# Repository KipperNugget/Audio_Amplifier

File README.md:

# ENGR 301 (Microelectronics Lab): Audio Amplifier

The goal of this project was to design, source components, and assemble an audio amplifier

EAGLE was utilized to design the pcb
LTspice was utilized for simulation

### Schematic

### Board
Please excuse the disgusting finish; attempted cleaning with isopropyl alcohol, but the flux continued to stain the board.

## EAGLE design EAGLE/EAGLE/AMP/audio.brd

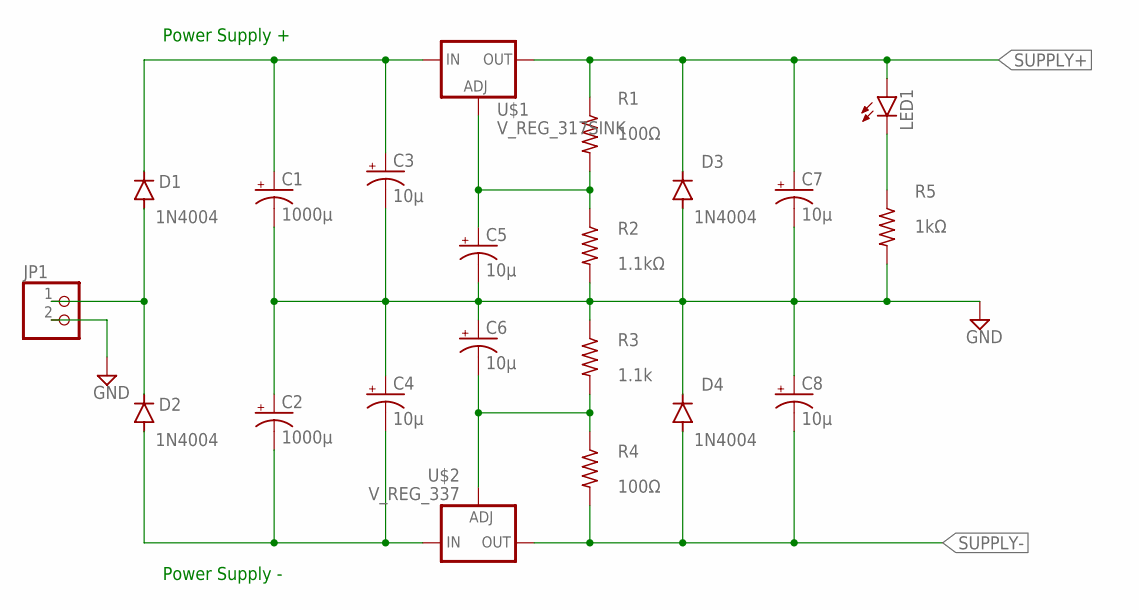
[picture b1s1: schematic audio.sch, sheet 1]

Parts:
C1, C2: 1000μ; E3,5-10
C3, C4, C5, C6, C7, C8: 10μ; E1,8-4
D1, D2, D3, D4: 1N4004; DO41-10
JP1: PINHD-1X2; 1X02
LED1: LED3MM
R1, R4: 100Ω; 0204/7
R2: 1.1kΩ; 0204/7
R3: 1.1k; 0204/7
R5: 1kΩ; 0204/7
U$1: V_REG_317SINK; TO220-ADJ
U$2: V_REG_337; TO220-ADJ-NEG

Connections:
GND: C1.-, C2.+, C3.-, C4.+, C5.-, C6.+, C7.-, C8.+, D3.A, D4.C, JP1.2, R2.2, R3.1, R5.2; also elsewhere on the board
unnamed: C1.+, C3.+, D1.C, U$1.IN
unnamed: C2.-, C4.-, D2.A, U$2.IN
unnamed: D1.A, D2.C, JP1.1
unnamed: C5.+, R1.2, R2.1, U$1.ADJ
unnamed: C6.-, R3.2, R4.1, U$2.ADJ
unnamed: LED1.K (C), R5.1
SUPPLY+: C7.+, D3.C, LED1.A, R1.1, U$1.OUT; also elsewhere on the board
SUPPLY-: C8.-, D4.A, R4.2, U$2.OUT; also elsewhere on the board

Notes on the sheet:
Power Supply -
Power Supply +

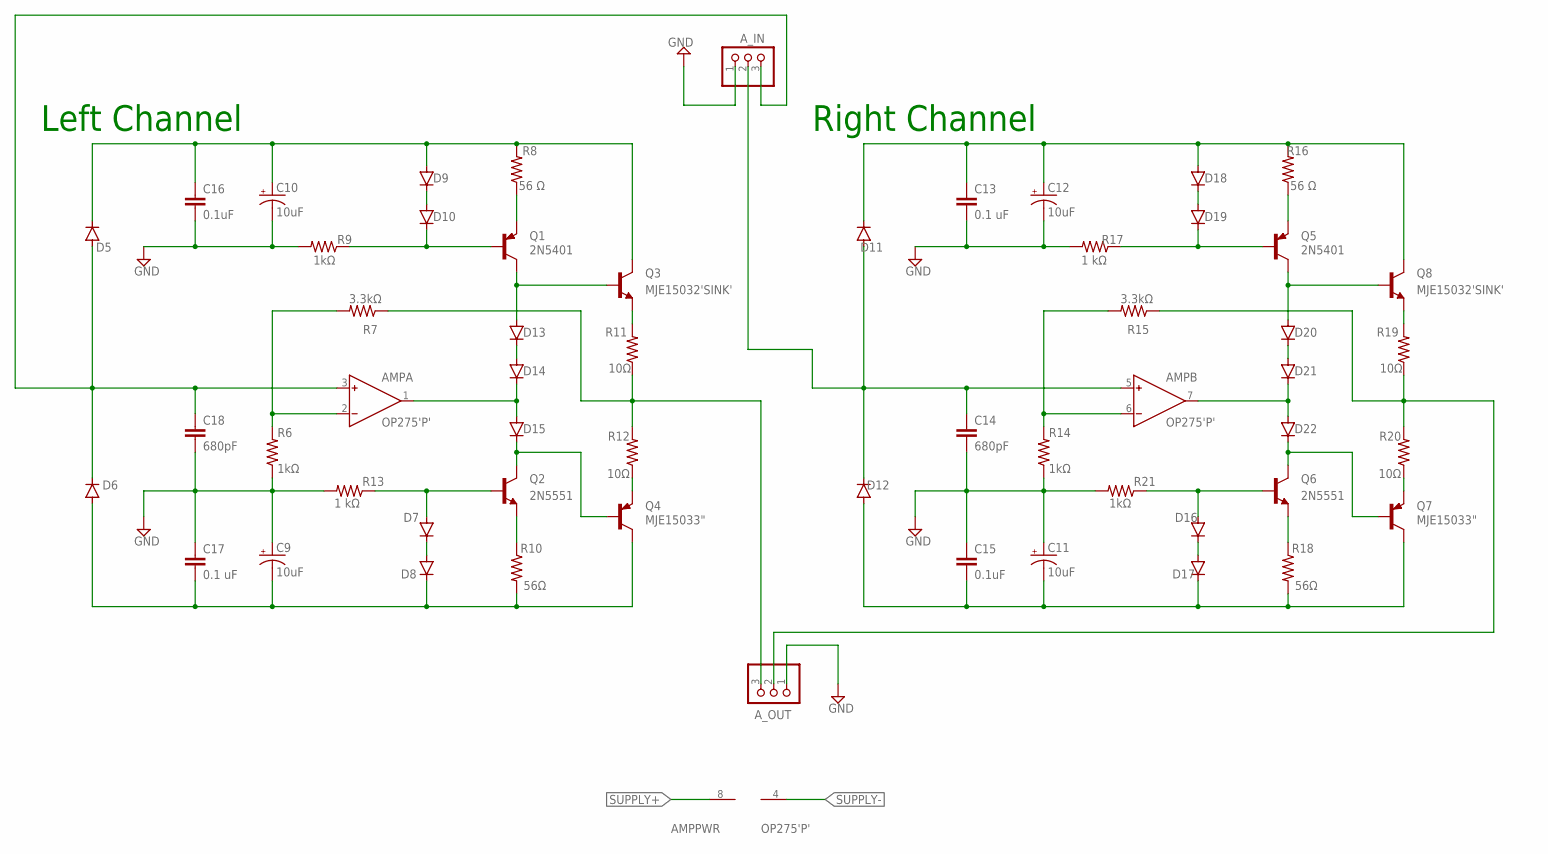
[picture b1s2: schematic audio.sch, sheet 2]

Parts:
AMP: OP275'P'; DIL08
A_IN: PINHD-1X3; 1X03
A_OUT: PINHD-1X3; 1X03
C9, C10, C11, C12: 10uF; E1,8-4
C13, C17: 0.1 uF; C2.5-3
C14, C18: 680pF; C2.5-3
C15, C16: 0.1uF; C2.5-3
D5, D6, D7, D8, D9, D10, D11, D12, D13, D14, D15, D16, D17, D18, D19, D20, D21, D22: 1N4148DO35-7; DO35-7
Q1, Q5: 2N5401
Q2, Q6: 2N5551
Q3, Q8: MJE15032'SINK'; TO220V-SINK
Q4, Q7: MJE15033"; TO220V-SINK
R6, R9, R14, R21: 1kΩ; 0204/7
R7, R15: 3.3kΩ; 0204/7
R8, R16: 56 Ω; 0204/7
R10, R18: 56Ω; 0204/7
R11, R12, R19, R20: 10Ω; 0204/7
R13, R17: 1 kΩ; 0204/7

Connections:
GND: A_IN.1, A_OUT.1, C9.+, C10.-, C11.+, C12.-, C13.2, C14.2, C15.1, C16.2, C17.1, C18.2, R6.1, R9.2, R13.2, R14.1, R17.2, R21.2; also elsewhere on the board
unnamed: AMP.3 (IN+), A_IN.3, C18.1, D5.A, D6.C
unnamed: C9.-, C17.2, D6.A, D8.C, Q4.2 (C), R10.2
unnamed: D7.C, D8.A
unnamed: C10.+, C16.1, D5.C, D9.A, Q3.2 (C), R8.2
unnamed: D9.C, D10.A
unnamed: AMP.2 (IN-), R6.2, R7.2
unnamed: Q1.E, R8.1
unnamed: D13.C, D14.A
unnamed: D13.A, Q1.C, Q3.1 (B)
unnamed: AMP.1 (OUT), D14.C, D15.A
unnamed: D15.C, Q2.C, Q4.1 (B)
unnamed: Q2.E, R10.1
unnamed: D10.C, Q1.B, R9.1
unnamed: Q3.3 (E), R11.2
unnamed: Q4.3 (E), R12.1
unnamed: D7.A, Q2.B, R13.1
unnamed: A_OUT.3, R7.1, R11.1, R12.2
unnamed: AMP.5 (IN+), A_IN.2, C14.1, D11.A, D12.C
unnamed: C11.-, C15.2, D12.A, D17.C, Q7.2 (C), R18.2
unnamed: D16.C, D17.A
unnamed: C12.+, C13.1, D11.C, D18.A, Q8.2 (C), R16.2
unnamed: D18.C, D19.A
unnamed: AMP.6 (IN-), R14.2, R15.2
unnamed: Q5.E, R16.1
unnamed: D20.C, D21.A
unnamed: D20.A, Q5.C, Q8.1 (B)
unnamed: AMP.7 (OUT), D21.C, D22.A
unnamed: D22.C, Q6.C, Q7.1 (B)
unnamed: D19.C, Q5.B, R17.1
unnamed: Q6.E, R18.1
unnamed: Q8.3 (E), R19.2
unnamed: Q7.3 (E), R20.1
unnamed: D16.A, Q6.B, R21.1
unnamed: A_OUT.2, R15.1, R19.1, R20.2
SUPPLY+: AMP.8 (V+); also elsewhere on the board
SUPPLY-: AMP.4 (V-); also elsewhere on the board

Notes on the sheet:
Left Channel
Right Channel

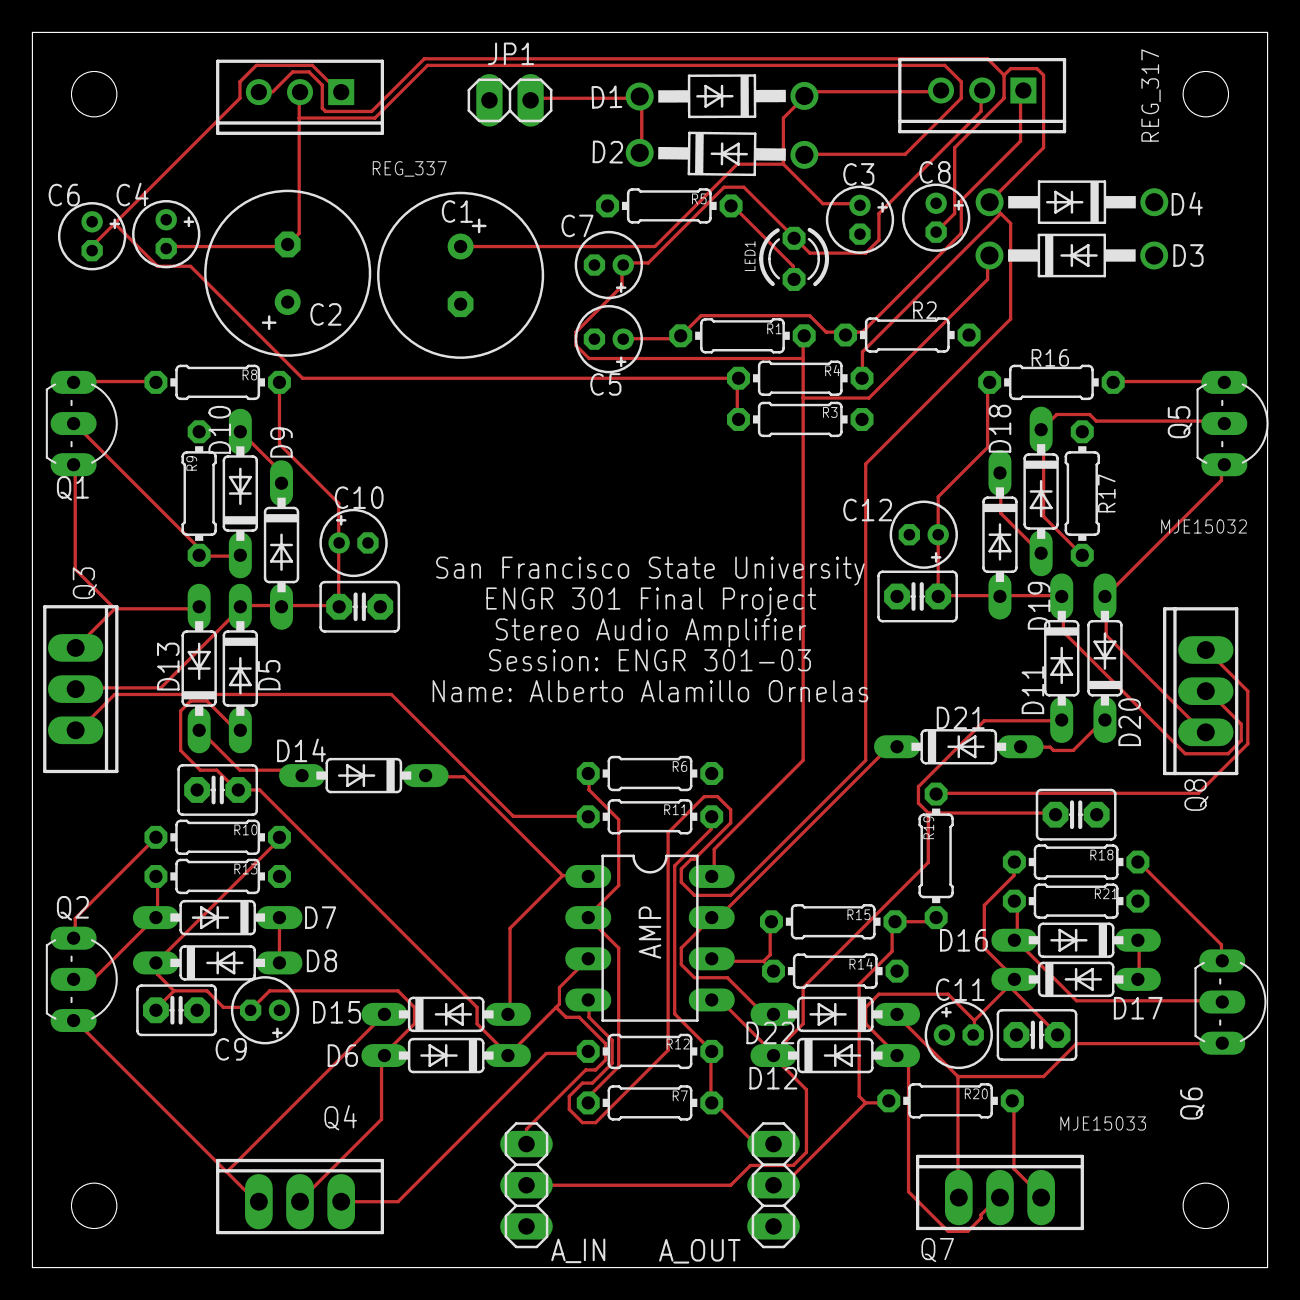
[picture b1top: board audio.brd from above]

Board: 2 copper layers, 76.2 x 76.2 mm, 76 parts (0 on the bottom side), 43 nets.
